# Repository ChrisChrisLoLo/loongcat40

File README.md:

# loongcat40
A 4x10 gasket mounted keyboard featuring a large OLED. A culmination of 5 years of learning.

## status
- v0.1 pcbs have been produced but not yet tested.
- v0.0 pcbs have been produced. v0.0 has been been tested.
  - The keyboard largely works, though GPIO20 requires an external pullup resistor. This may have been due to the rp2040 dev board I was using.

## about

## case
All of the case files you need can be found in the `case` directory.

## pcb
You can find the PCB source files in the `pcb` folder. The BOM files can be found in this folder.

## directory structure
- `case`
    You can find the files you need in this folder to print out a case for the keyboard
- `drafts`
    Stores any KLE or intermediate information used in making the case
- `pcb`
    Kicad project relating to the project

## BOM
- 1 PCB
- 40 hotswap sockets
- 40 diodes
- 1 2.08" OLED LCD (SH1122)
- 3mm poron gasket strips (80mm x 3mm x 4mm)
- 1 Raspberry Pi Pico 1
- 3D printed parts
  - 4 TPU oled standoffs
    - used to make sure that the oled is aligned when soldering
  - 2 PLA plates
  - 1 PLA case bottom
  - 1 PLA casetop
- 12 5mm M2 screws
- 4 rubber bumpons

## assembly
- Assemble the PCB without the oled
  - the Pico should be soldered via castellated pins. Male pin headers should _not_ be used 
- Put the 4 TPU oled standoffs onto the oled module. These standoffs will help align the oled
- Solder the oled to the pcb. The oled module should be on the other side of the board such that it's on the opposite side 
- Put the poron gaskets onto the plate
- Put the keys through the plate and onto the PCB
- Put the PCB onto the top of the case
- Put the bottom of the case on
- Screw in the bottom of the case
  - Note that screwing the screws for the first time may take some force, as the screws will be threading the plastic of the top
- Put bumpers on the bottom of the case
- Done!

## firmware
You can find the QMK firmware for this project here: https://github.com/ChrisChrisLoLo/qmk_firmware/tree/loongcat40

## acknowledgements

Thank you to [NextPCB](https://www.nextpcb.com/?code=ChristianLo) and all of my Github Sponsors for sponsoring and supporting this project!

Big thank you to [@suh_ga](https://x.com/suh_ga) for the fantastic artwork used and displayed on this keyboard! Please check her out at https://twitter.com/suh_ga!

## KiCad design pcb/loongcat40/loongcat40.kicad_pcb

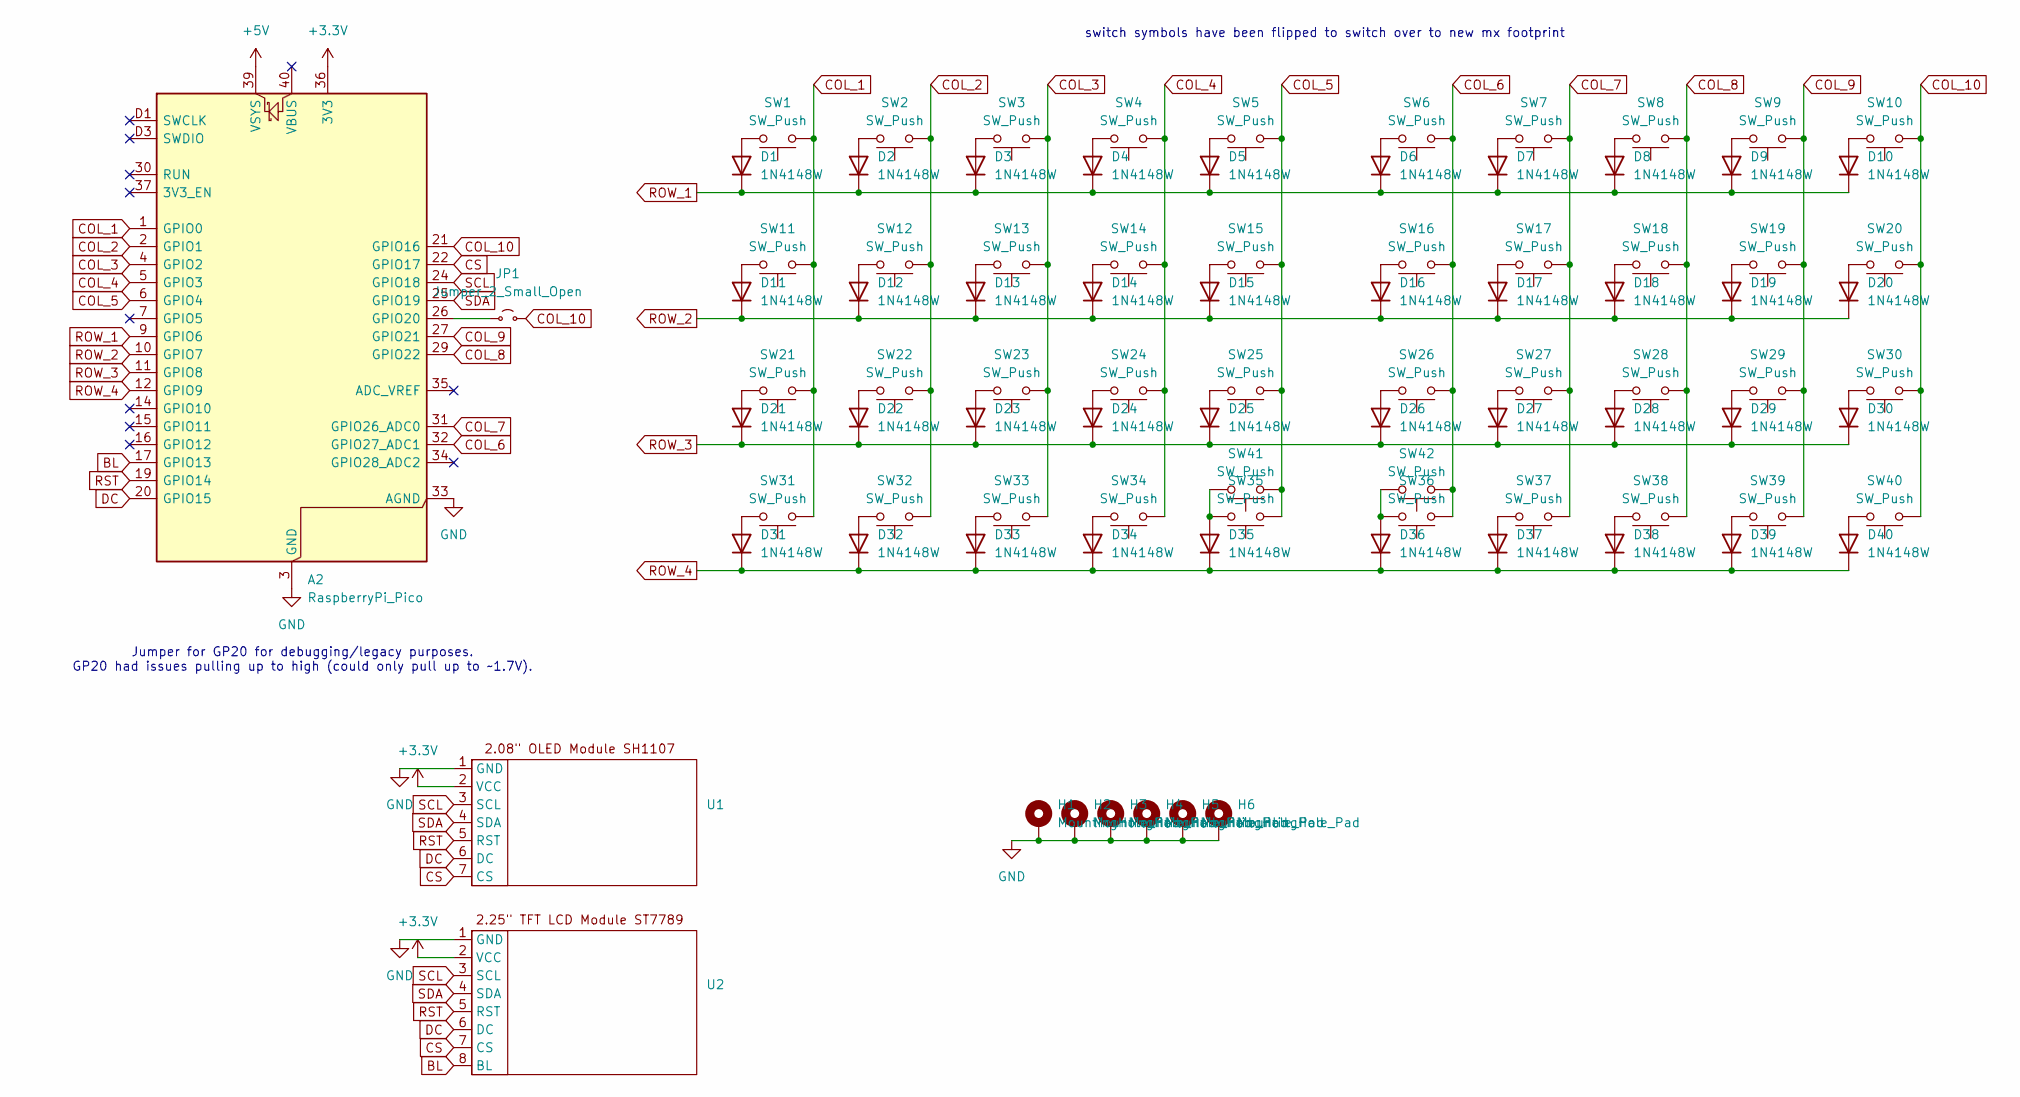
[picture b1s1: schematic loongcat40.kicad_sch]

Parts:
A2: RaspberryPi_Pico; RaspberryPi_Pico_Common_Unspecified
D1, D2, D3, D4, D5, D6, D7, D8, D9, D10, D11, D12, D13, D14, D15, D16, D17, D18, D19, D20, D21, D22, D23, D24, D25, D26, D27, D28, D29, D30, D31, D32, D33, D34, D35, D36, D37, D38, D39, D40: 1N4148W; D_SOD-123
H1, H2, H3, H4, H5, H6: MountingHole_Pad; MountingHole_2.2mm_M2_Pad
JP1: Jumper_2_Small_Open; SolderJumper-2_P1.3mm_Open_RoundedPad1.0x1.5mm
SW1, SW2, SW3, SW4, SW5, SW6, SW7, SW8, SW9, SW10, SW11, SW12, SW13, SW14, SW15, SW16, SW17, SW18, SW19, SW20, SW21, SW22, SW23, SW24, SW25, SW26, SW27, SW28, SW29, SW30, SW31, SW32, SW33, SW34, SW35, SW36, SW37, SW38, SW39, SW40, SW41, SW42: SW_Push; Kailh_socket_MX
U1: SH1122_2.08inch
U2: ST7789_2.25inch

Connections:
+3.3V: A2.36 (3V3), U1.2 (VCC), U2.2 (VCC)
+5V: A2.39 (VSYS)
BL: A2.17 (GPIO13), U2.8 (BL)
COL_1: A2.1 (GPIO0), SW1.1, SW11.1, SW21.1, SW31.1
COL_2: A2.2 (GPIO1), SW2.1, SW12.1, SW22.1, SW32.1
COL_3: A2.4 (GPIO2), SW3.1, SW13.1, SW23.1, SW33.1
COL_4: A2.5 (GPIO3), SW4.1, SW14.1, SW24.1, SW34.1
COL_5: A2.6 (GPIO4), SW5.1, SW15.1, SW25.1, SW35.1, SW41.1
COL_6: A2.32 (GPIO27_ADC1), SW6.1, SW16.1, SW26.1, SW36.1, SW42.1
COL_7: A2.31 (GPIO26_ADC0), SW7.1, SW17.1, SW27.1, SW37.1
COL_8: A2.29 (GPIO22), SW8.1, SW18.1, SW28.1, SW38.1
COL_9: A2.27 (GPIO21), SW9.1, SW19.1, SW29.1, SW39.1
COL_10: A2.21 (GPIO16), JP1.2 (B), SW10.1, SW20.1, SW30.1, SW40.1
CS: A2.22 (GPIO17), U1.7 (CS), U2.7 (CS)
DC: A2.20 (GPIO15), U1.6 (DC), U2.6 (DC)
GND: A2.3 (GND), A2.8 (GND), A2.13 (GND), A2.18 (GND), A2.23 (GND), A2.28 (GND), A2.33 (AGND), A2.38 (GND), A2.D2 (GND), H1.1, H2.1, H3.1, H4.1, H5.1, H6.1, U1.1 (GND), U2.1 (GND)
unnamed: A2.26 (GPIO20), JP1.1 (A)
unnamed: D1.2 (A), SW1.2
unnamed: D2.2 (A), SW2.2
unnamed: D3.2 (A), SW3.2
unnamed: D4.2 (A), SW4.2
unnamed: D5.2 (A), SW5.2
unnamed: D6.2 (A), SW6.2
unnamed: D7.2 (A), SW7.2
unnamed: D8.2 (A), SW8.2
unnamed: D9.2 (A), SW9.2
unnamed: D10.2 (A), SW10.2
unnamed: D11.2 (A), SW11.2
unnamed: D12.2 (A), SW12.2
unnamed: D13.2 (A), SW13.2
unnamed: D14.2 (A), SW14.2
unnamed: D15.2 (A), SW15.2
unnamed: D16.2 (A), SW16.2
unnamed: D17.2 (A), SW17.2
unnamed: D18.2 (A), SW18.2
unnamed: D19.2 (A), SW19.2
unnamed: D20.2 (A), SW20.2
unnamed: D21.2 (A), SW21.2
unnamed: D22.2 (A), SW22.2
unnamed: D23.2 (A), SW23.2
unnamed: D24.2 (A), SW24.2
unnamed: D25.2 (A), SW25.2
unnamed: D26.2 (A), SW26.2
unnamed: D27.2 (A), SW27.2
unnamed: D28.2 (A), SW28.2
unnamed: D29.2 (A), SW29.2
unnamed: D30.2 (A), SW30.2
unnamed: D31.2 (A), SW31.2
unnamed: D32.2 (A), SW32.2
unnamed: D33.2 (A), SW33.2
unnamed: D34.2 (A), SW34.2
unnamed: D35.2 (A), SW35.2, SW41.2
unnamed: D36.2 (A), SW36.2, SW42.2
unnamed: D37.2 (A), SW37.2
unnamed: D38.2 (A), SW38.2
unnamed: D39.2 (A), SW39.2
unnamed: D40.2 (A), SW40.2
ROW_1: A2.9 (GPIO6), D1.1 (K), D2.1 (K), D3.1 (K), D4.1 (K), D5.1 (K), D6.1 (K), D7.1 (K), D8.1 (K), D9.1 (K), D10.1 (K)
ROW_2: A2.10 (GPIO7), D11.1 (K), D12.1 (K), D13.1 (K), D14.1 (K), D15.1 (K), D16.1 (K), D17.1 (K), D18.1 (K), D19.1 (K), D20.1 (K)
ROW_3: A2.11 (GPIO8), D21.1 (K), D22.1 (K), D23.1 (K), D24.1 (K), D25.1 (K), D26.1 (K), D27.1 (K), D28.1 (K), D29.1 (K), D30.1 (K)
ROW_4: A2.12 (GPIO9), D31.1 (K), D32.1 (K), D33.1 (K), D34.1 (K), D35.1 (K), D36.1 (K), D37.1 (K), D38.1 (K), D39.1 (K), D40.1 (K)
RST: A2.19 (GPIO14), U1.5 (RST), U2.5 (RST)
SCL: A2.24 (GPIO18), U1.3 (SCL), U2.3 (SCL)
SDA: A2.25 (GPIO19), U1.4 (SDA), U2.4 (SDA)

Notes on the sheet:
Jumper for GP20 for debugging/legacy purposes. GP20 had issues pulling up to high (could only pull up to ~1.7V).
switch symbols have been flipped to switch over to new mx footprint

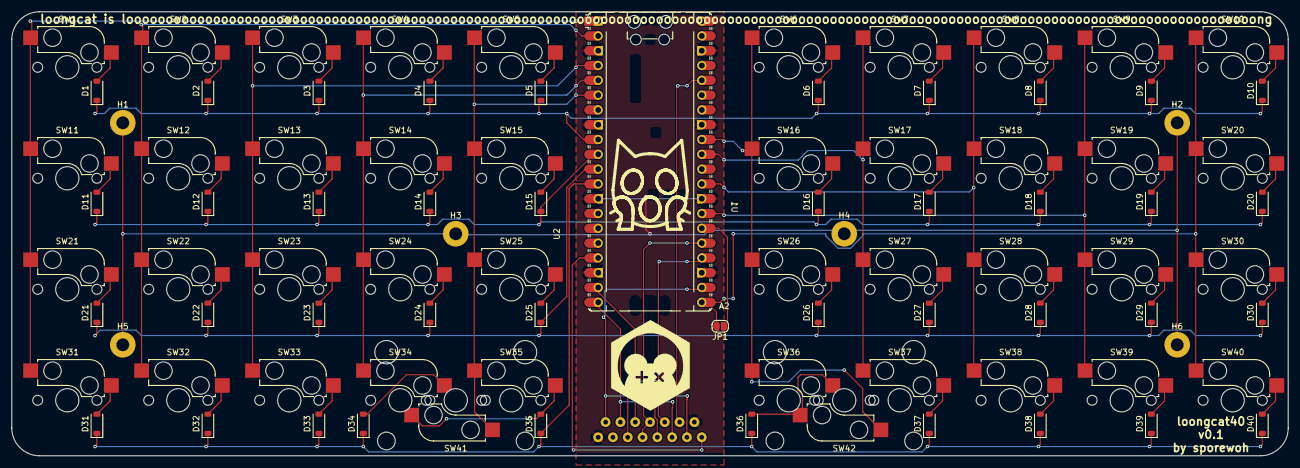
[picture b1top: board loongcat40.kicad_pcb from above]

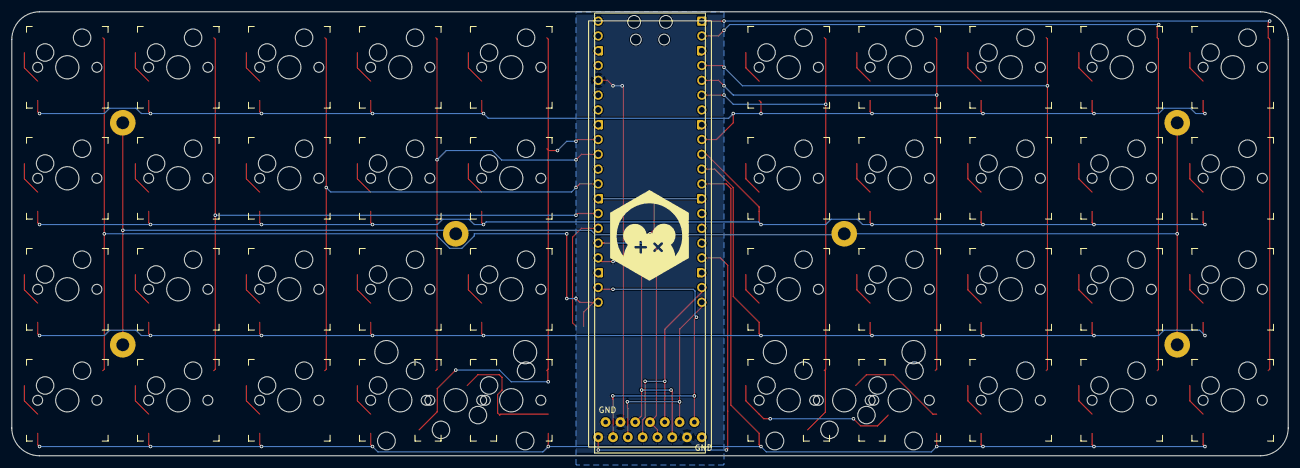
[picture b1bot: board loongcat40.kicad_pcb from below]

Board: 2 copper layers, 219.1 x 76.2 mm, 92 parts (43 on the bottom side), 63 nets.

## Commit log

2025-09-25 init pcb
2025-09-25 add kle; create init pcb design
2025-09-26 position parts on pcb
2025-10-03 create outputs; init keyboard case
2025-10-05 add init case bottom
2025-10-05 add init base case top
2025-10-05 add keyswitches as submodule
2025-10-05 add standoff
2025-10-06 update standoffs and case bottom
2025-10-06 tighten tolerances
2025-10-07 refine case and standoffs
2025-10-13 reduce ground plane
2025-10-13 increase shroud length
2025-10-13 remove pcb outputs
2025-10-13 update gitignore to ignore outputs and backup files
2025-10-13 add lcd standoff length
2025-10-14 add images
2025-10-15 add oled mod cover top
2025-10-15 connect ground holes to pico
2025-10-16 add soldering jig; init lcd top
2025-10-18 update pcb to support 2U stabilizers, update col10 pin
2025-10-18 update lcd fillet; add lcd square standoff
2025-11-16 add outputs
2025-11-16 add photos
2025-11-16 update image paths
2025-11-16 update freecad models
2025-11-21 Fix formatting of acknowledgements section in README
2025-12-01 Update sponsorship link for NextPCB
